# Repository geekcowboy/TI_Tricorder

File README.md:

Prototyping the Future: The Mark I Tricorder Project

For 50 decades, Star Trek has served as an inspiration for engineers and makers alike. Many of the tech concepts of 1960s science fiction has turned into 21st century everyday reality.  One of the most beloved ideas was the all-in-one Tricorder that let the crew ascertain the status of countless environmental factors. The Tricorder of the Captain Kirk and Mr. Spock may still be a few generations away, but what if the Mark I version of the Tricorder was invented tody?

This project presents one intriguing possibility.  Highlighting the amazing micrcontroller and sensor technology of today, we've built a Mark I Tricorder prototype.  Leveraging the out-of-this-world capabilities of the new TI MSP432P401R LaunchPad, we've put a ton of sensors in a conventient BoosterPack form factor.

Some highlights of the Tricorder BoosterPack:

- HDC1000 Humidity Sensor
- LMT70 Temperature Sensor
- OPT3001 Ambient Light Sensor
- MAG3110 Magnetometer
- LMP91000 Electrochemical Sensor Interface
- PGA900 Programmable Resistive Sensing Conditioner
- microSD Card reader
- Peripheral Module (Pmod) Type I GPIO Interface 
- 2 user defined buttons / 1 reset button
- 2 user defined LEDs / 1 power indicator LED

Coming Soon:  Shopping Cart BOM @ Mouser Electronics

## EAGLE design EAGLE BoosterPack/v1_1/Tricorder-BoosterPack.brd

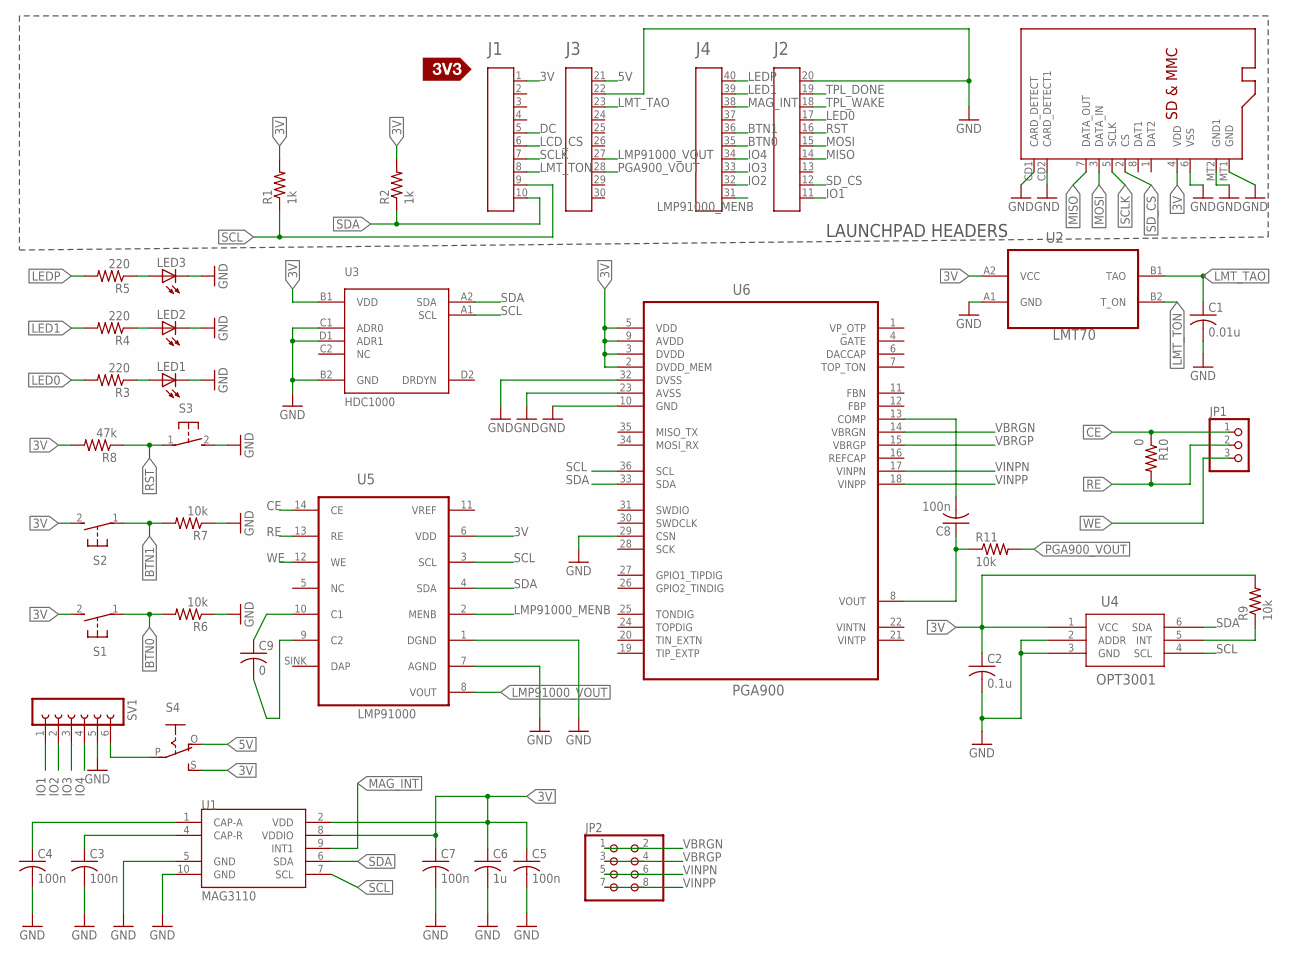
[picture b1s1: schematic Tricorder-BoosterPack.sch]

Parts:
A1: HEADER4X10-BOOSTERPACK; 4X10-BOOSTERPACK
C1: 0.01u; C0603
C2: 0.1u; C0603
C3, C4, C5, C7, C8: 100n; C0603
C6: 1u; C0603
C9: 0; C0603
JP1: PINHD-1X3CB; 1X03-CLEANBIG
JP2: PINHD-2X4; 2X04
LED1, LED2, LED3: LEDCHIPLED_0603; CHIPLED_0603
R1, R2: 1k; R0603
R3, R4, R5: 220; R0603
R6, R7, R9, R11: 10k; R0603
R8: 47k; R0603
R10: 0; R0603
S1, S2, S3: 31-XX; B3F-31XX
S4: EG1218S; EG1218
SV1: FE06-1; FE06
U1: MAG3110; DFN-10
U2: LMT70LMT70; BGA4C40P2X2_77X77X50
U3: HDC1000; DSBGA_8_YPA
U4: OPT3001; DPK6
U5: LMP91000; WFDFN-14; DIGIKEY LMP91000
U6: PGA900; QFN50P600X600X90-37N
U7: MICROSD
U$3: SILK_3V3_TAG

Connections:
3V: A1.1, C2.1, C5.1, C6.1, C7.1, R1.2, R2.2, R8.2, R9.2, S1.2 (S), S2.2 (S), S4.S, U1.2 (VDD), U1.8 (VDDIO), U2.A2 (VCC), U3.B1 (VDD), U4.1 (VCC), U5.6 (VDD), U6.2 (DVDD_MEM), U6.3 (DVDD), U6.5 (VDD), U6.9 (AVDD), U7.4 (VDD)
5V: A1.21, S4.O
BTN0: A1.35, R6.2, S1.1
BTN1: A1.36, R7.2, S2.1
CE: JP1.1, R10.1, U5.14 (CE)
DC: A1.5
GND: A1.20, A1.22, C1.2, C2.2, C3.2, C4.2, C5.2, C6.2, C7.2, LED1.C, LED2.C, LED3.C, R6.1, R7.1, S3.2 (S), SV1.5, U1.5 (GND), U1.10 (GND), U2.A1 (GND), U3.B2 (GND), U3.C1 (ADR0), U3.D1 (ADR1), U4.2 (ADDR), U4.3 (GND), U5.1 (DGND), U5.7 (AGND), U6.10 (GND), U6.23 (AVSS), U6.29 (CSN), U6.32 (DVSS), U7.6 (VSS), U7.CD1 (CARD_DETECT), U7.CD2 (CARD_DETECT1), U7.MT1 (GND), U7.MT2 (GND1)
IO1: A1.11, SV1.1
IO2: A1.32, SV1.2
IO3: A1.33, SV1.3
IO4: A1.34, SV1.4
LCD_CS: A1.6
LED0: A1.17, R3.2
LED1: A1.39, R4.2
LEDP: A1.40, R5.2
LMP91000_MENB: A1.31, U5.2 (MENB)
LMP91000_VOUT: A1.27, U5.8 (VOUT)
LMT_TAO: A1.23, C1.1, U2.B1 (TAO)
LMT_TON: A1.8, U2.B2 (T_ON)
MAG_INT: A1.38, U1.9 (INT1)
MISO: A1.14, U7.7 (DATA_OUT)
MOSI: A1.15, U7.3 (DATA_IN)
unnamed: LED1.A, R3.1
unnamed: LED2.A, R4.1
unnamed: LED3.A, R5.1
unnamed: S4.P, SV1.6
unnamed: R9.1, U4.5 (INT)
unnamed: C9.1, U5.10 (C1)
unnamed: C3.1, U1.4 (CAP-R)
unnamed: C4.1, U1.1 (CAP-A)
unnamed: C8.2, U6.13 (COMP)
unnamed: C9.2, U5.9 (C2)
unnamed: C8.1, R11.1, U6.8 (VOUT)
PGA900_VOUT: A1.28, R11.2
RE: JP1.2, R10.2, U5.13 (RE)
RST: A1.16, R8.1, S3.1
SCL: A1.9, R1.1, U1.7 (SCL), U3.A1 (SCL), U4.4 (SCL), U5.3 (SCL), U6.36 (SCL)
SCLK: A1.7, U7.5 (SCLK)
SDA: A1.10, R2.1, U1.6 (SDA), U3.A2 (SDA), U4.6 (SDA), U5.4 (SDA), U6.33 (SDA)
SD_CS: A1.12, U7.2 (CS)
TPL_DONE: A1.19
TPL_WAKE: A1.18
VBRGN: JP2.1, JP2.2, U6.14 (VBRGN)
VBRGP: JP2.3, JP2.4, U6.15 (VBRGP)
VINPN: JP2.5, JP2.6, U6.17 (VINPN)
VINPP: JP2.7, JP2.8, U6.18 (VINPP)
VREF: U5.11 (VREF)
WE: JP1.3, U5.12 (WE)

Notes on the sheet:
LAUNCHPAD HEADERS

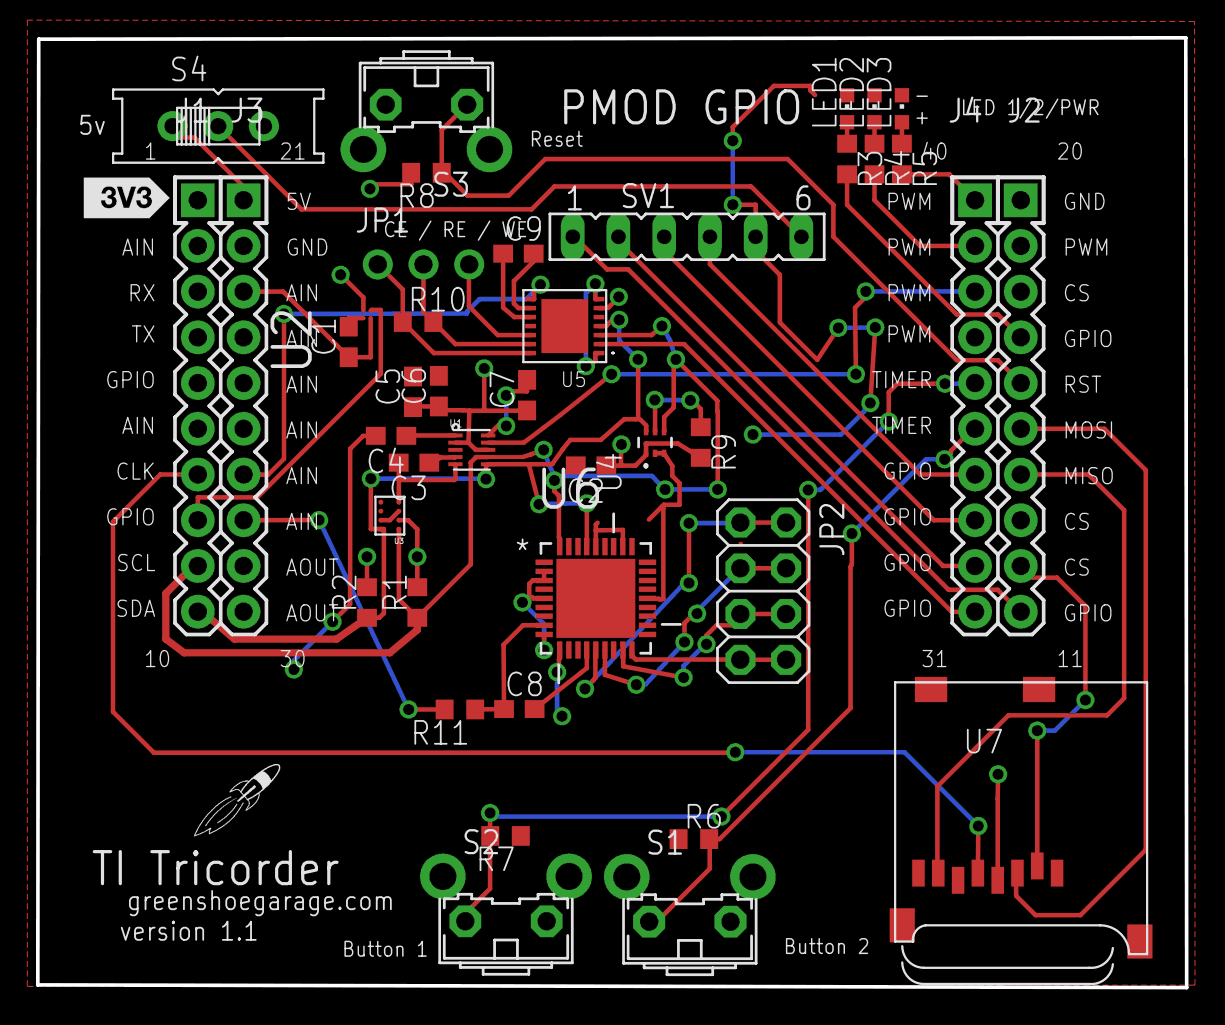
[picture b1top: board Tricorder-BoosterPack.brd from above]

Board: 2 copper layers, 63.8 x 52.8 mm, 40 parts (0 on the bottom side), 43 nets.

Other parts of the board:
U$2: LOGO-ROCKET

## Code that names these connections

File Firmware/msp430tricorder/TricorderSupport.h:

//
//  TricorderSupport
//  Example for library for MSP432P401R-based Tricorder BoosterPack
//
//
//  Date   :  Sep 12, 2015
//  Version:  1.00
//  File   :  TricorderSupport.h
//
//  Licence CC = BY SA NC
//
//  Use of Clock from Galaxia library for MSP432 proposed by ReiVilo
//

#ifndef TricorderSupport_h
#define TricorderSupport_h

//
// #DEFINES
//
#define numSensors 6
#define debounceDelay 175

#define HDC1000_id 0
#define LMT70_id 1
#define OPT3001_id 2
#define MAG3110_id 3
#define LMP91000_id 4
#define PGA900_id 5

#define leftButton P6_7         //pin35  P6_7
#define rightButton P6_6        //pin36  P6_6
#define powerLED P2_7           //pin40  P2_7
#define LED0 P5_7               //pin17  P5_7
#define LED1 P2_6               //pin39  P2_6

#define PMOD0 P3_6             //pin11
#define PMOD1 P3_5             //pin32
#define PMOD2 P5_1             //pin33
#define PMOD3 P2_3             //pin34

#define LMT70_TON P4_6         //pin8
#define LMT70_TAO A14          //pin23    P6_1
#define LMP91000_VOUT A8       //pin27    P4_5
#define PGA900_VOUT A6         //pin28    P4_7
#define LMP91000_MENB P3_7     //pin31
#define MAG3110_INT P2_4       //pin38

#define SCL_pin P6_5           //pin9
#define SDA_pin P6_4           //pin10

#define SD_CS P5_2             //pin12

const float LMT70_AMul = -0.00000000180963;
const float LMT70_BMul = -0.000003325395;
const float LMT70_CMul = -0.1814103;
const float LMT70_DMul = 205.5894;


//TricorderSupport Class
class TricorderSupport {
public:
    TricorderSupport();
    float read_LMT70();
    float read_HDC1000();
    float read_OPT3001();
    float read_MAG3110();
    float read_PGA900();
    float read_LMP91000();

private:
};


#endif

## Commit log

2015-07-03 Create README.md
    init release
2015-07-04 Schematic Capture v001
    Initial schematic capture of major external/large components (e.g.
    switch, PMOD interface). Initial PCB layout with copper fill for GND.
    No routing.
2015-07-05 Pin Assignment .xlsx
    Lists of pin assignment for devices to the BoosterPack standard
2015-09-12 SCH/BRD update, Init firmware
    Added 4 main sensors to schematic and PMOD, buttons, LEDs, necessary
    peripheral components.
    Initial firmware release.
2015-09-13 Initial enclosure design
    First pass at an enclosure for the Tricorder project. Designed to be
    3D printed.
2015-09-14 Hardware Lock
    Hardware design locked for TI review and approval. 3D CAD files
    updated to reflect new PCB dimensions.
2015-09-14 STL Files
    Added STL files for 3D printed enclosure.
2015-09-21 LMP91000 and Alphasense O2-A1 Sensor
    Reconfigured board to include a TI LMP91000 gas sensor I2C interface
    chip and placeholder for Alphasense O2-A1 oxygen sensor
2015-09-21 O2 Sensor Moved Offboard
    Replace onboard O2 sensor with header pins to allow for off board
    placement of sensor. Eagle files revised as well as documentation files.
2015-09-21 Updated PCB STL file
    Updated PCB STL file
2015-09-25 v2 PCB Layout
    Revamped the PCB layout to make room for a PGA900 and Honeywell
    Pressure Sensor
2015-09-27 PGA900 w/ Male Headers for Resistive Senor Offboard
    Added the PGA900 Programmable Resistive Sensing Conditioner IC and male
    header to allow external resistive pressure sensor
2015-09-27 Added components to 3D visualization
    Added components to 3D visualization such as ICs, switches, buttons,
    and LEDs
2015-09-29 Completed PGA900 circuit, add microSD card reader
    Completed PGA900 circuit, add microSD card reader
2015-10-02 Hardware Design Lock
    Short of finding any showstopper bugs, the hardware design and BOM is
    locked.
2015-10-02 Update Documentation
    Updated documentation to reflect final hardware design.
2015-10-11 MAG3110 Circuit Fix
    Removed R10, renumbered components
2015-10-16 Revised BOM
2015-10-28 v1.0 Hardware sent to Fab
    Removed rev1 and locked rev2 design files, hardware sent to fab house.
2015-10-31 BOM Update
2015-11-03 TricorderSupport.h/.cpp Created
    Cleaning up code to ensure readability
2015-11-03 BOM revision
2015-11-03 read_LMT70() Function Started
2015-11-04 revised TricorderSupport.h
2015-11-06 updated documentation
2015-11-06 removed old libraries
2015-11-06 minor code tweaks
2015-11-06 cleaned up folder names
2015-11-11 Operating Concepts as Published
2015-11-11 deleted unneeded files
2015-11-14 v1.1
    board corrections and code corrections
2015-11-14 v1.1 BOM Updates
2015-11-14 Added v1.1 support libraries
2015-11-15 new enclosure design (v1.1)
2015-11-15 updated document names to reflect new version (v1.1)
2015-11-15 new gerber and image files
2015-11-22 3D files revised
2016-01-05 revised brd and sch

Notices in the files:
parts and their libraries:
SparkFun-Sensors: Licensing: Creative Commons ShareAlike 4.0 International - https://creativecommons.org/licenses/by-sa/4.0
